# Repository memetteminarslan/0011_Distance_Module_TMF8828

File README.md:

# 0011_Distance_Module_TMF8828
You are seeing a large number of widely used Distance modules in electronic development kits. More information coming soon...

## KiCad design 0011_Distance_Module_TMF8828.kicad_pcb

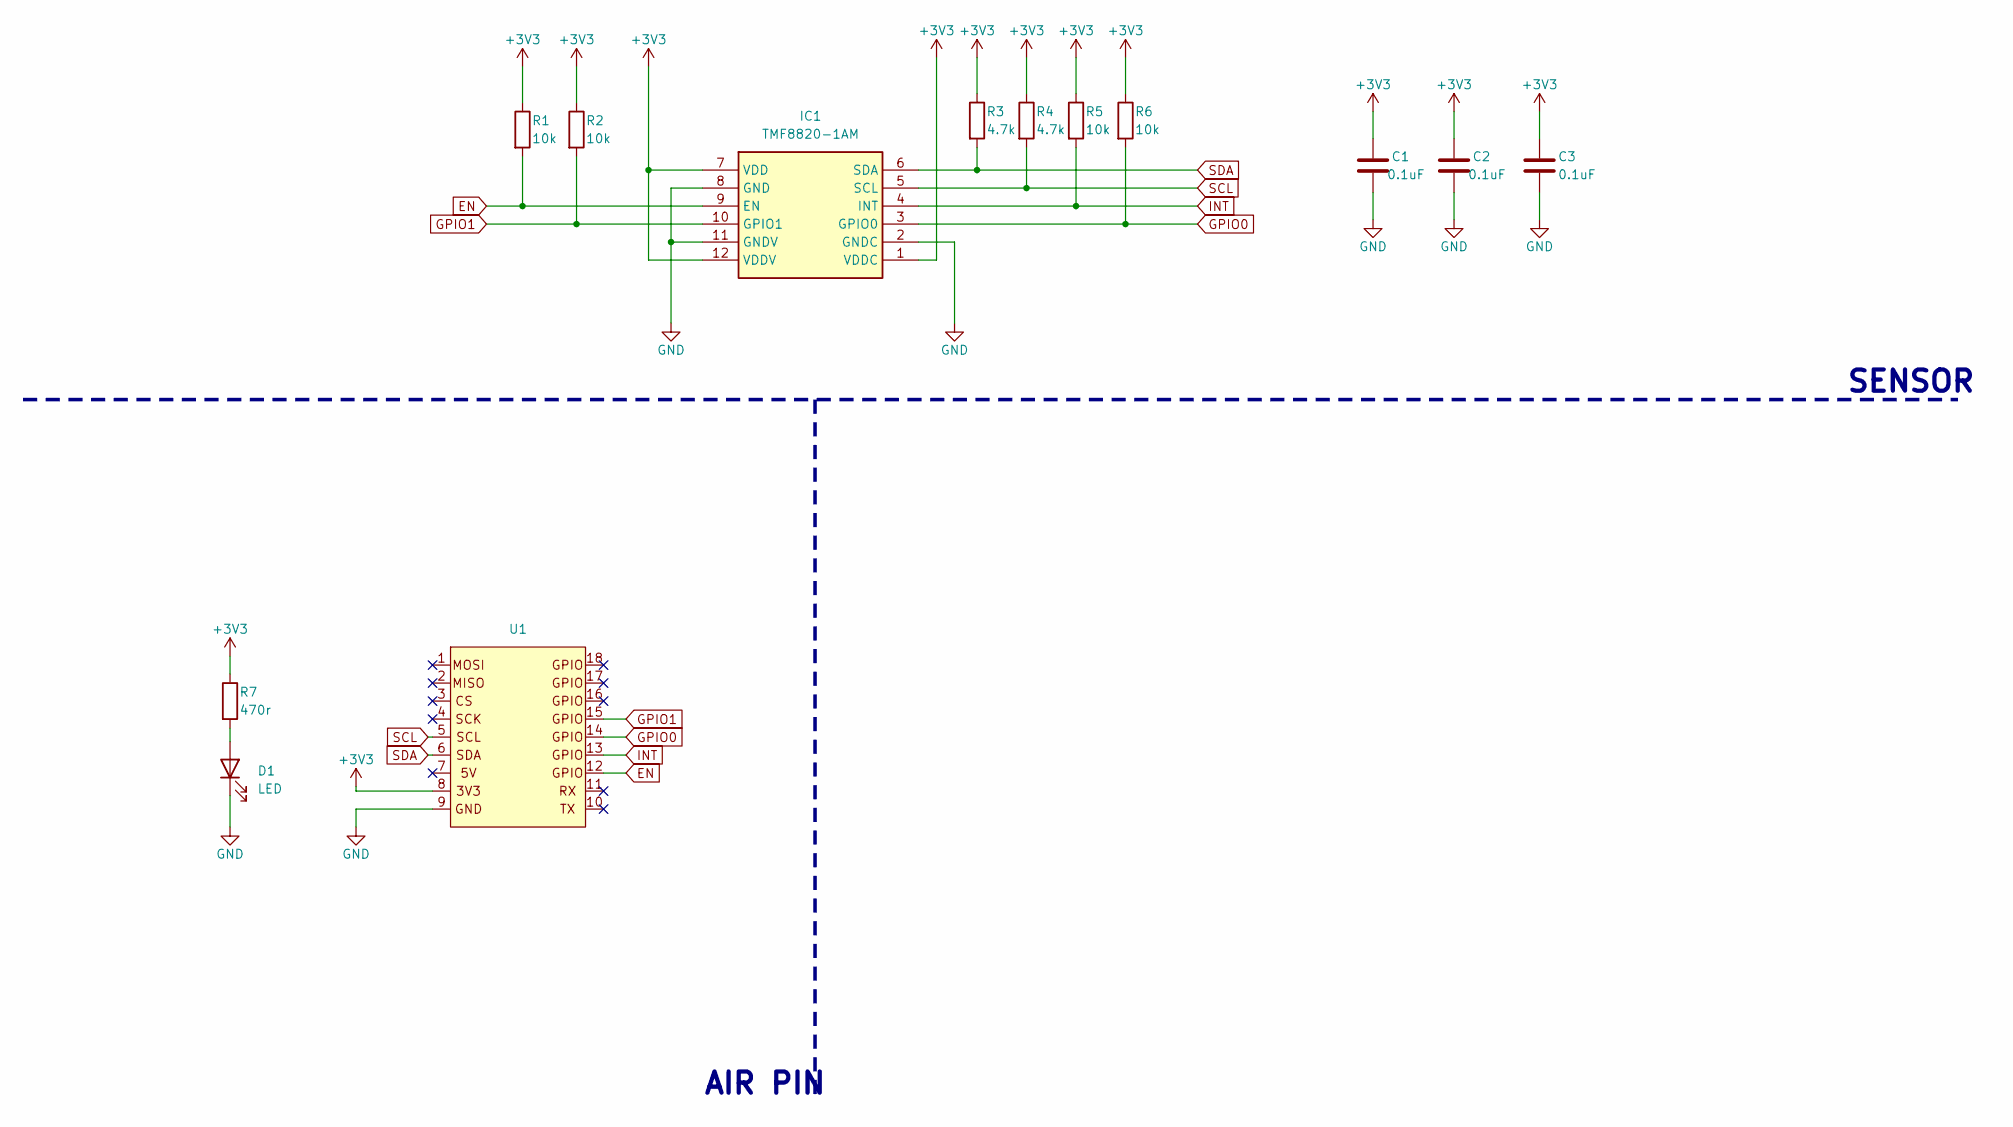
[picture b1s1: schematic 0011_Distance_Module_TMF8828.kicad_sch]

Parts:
C1, C2, C3: 0.1uF; C_0603_1608Metric
D1: LED; LED_0603_1608Metric
IC1: TMF8820-1AM; TMF88201AM; Manufacturer_Part_Number TMF8820-1AM
R1, R2, R5, R6: 10k; R_0603_1608Metric
R3, R4: 4.7k; R_0603_1608Metric
R7: 470r; R_0603_1608Metric
U1: pin_header

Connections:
+3V3: C1.1, C2.1, C3.1, IC1.1 (VDDC), IC1.7 (VDD), IC1.12 (VDDV), R1.1, R2.1, R3.1, R4.1, R5.1, R6.1, R7.1, U1.8
EN: IC1.9 (EN), R1.2, U1.12
GND: C1.2, C2.2, C3.2, D1.1 (K), IC1.2 (GNDC), IC1.8 (GND), IC1.11 (GNDV), U1.9
GPIO0: IC1.3 (GPIO0), R6.2, U1.14
GPIO1: IC1.10 (GPIO1), R2.2, U1.15
INT: IC1.4 (INT), R5.2, U1.13
unnamed: D1.2 (A), R7.2
SCL: IC1.5 (SCL), R4.2, U1.5
SDA: IC1.6 (SDA), R3.2, U1.6

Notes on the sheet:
SENSOR
AIR PIN

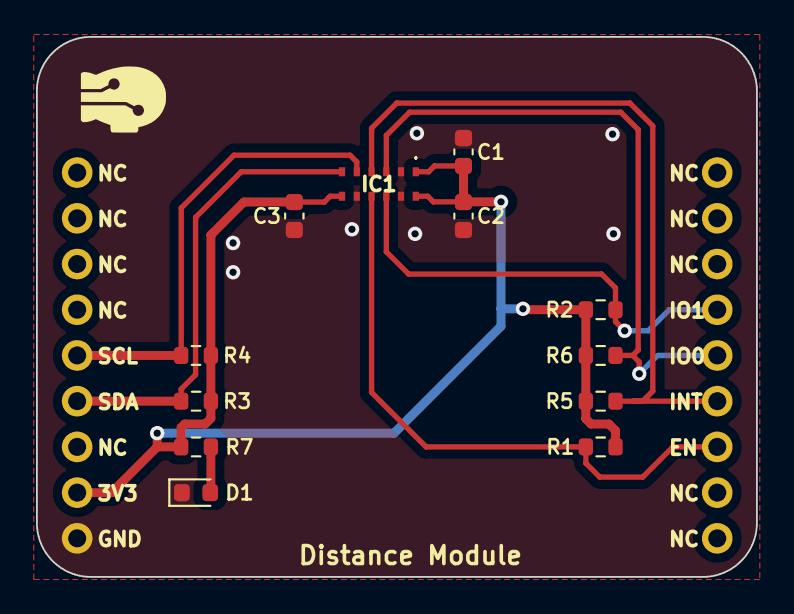
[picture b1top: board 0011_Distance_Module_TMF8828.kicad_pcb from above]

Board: 2 copper layers, 40.0 x 30.0 mm, 13 parts (0 on the bottom side), 9 nets.
